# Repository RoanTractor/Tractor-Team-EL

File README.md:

# Tractor-Team-EL
Tractor team electrical , experts in killing electrical gremlins and using black powder.

To learn how to contribute
Head to Introduction and read the Introduction To Git

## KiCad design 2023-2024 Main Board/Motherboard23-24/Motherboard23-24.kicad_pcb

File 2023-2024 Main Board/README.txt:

Things Staying the same
	Safety Circuit - Not Touching That
	Safety Start - Not Touching That

Things Changing

	Minor adjustments to 
		Throttle Control
		Steering Control
	
	Layout Changes
		Bigger Board (more height, same length)

 5V Protection

	5V goes through diode to prevent the 5v and GND being swapped and messing things up
	goes through thermistor to prevent spikes of current
	Zener Diode prevents overvoltage (over 5.1V)

	Possibly Fix Fuse (i dont know if it really does anything at this moment)

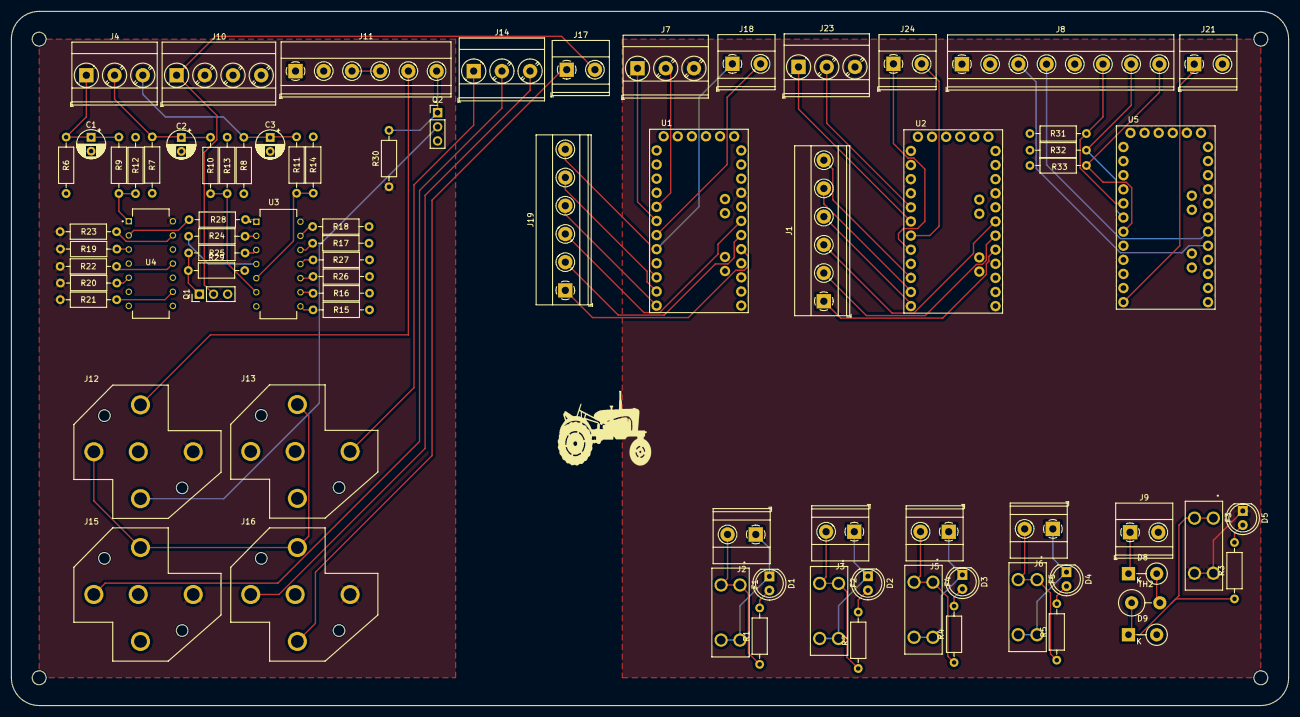
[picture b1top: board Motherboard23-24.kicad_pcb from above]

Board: 2 copper layers, 230.0 x 125.0 mm, 78 parts (0 on the bottom side), 81 nets.

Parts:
C1, C2, C3: 0.1µF; CP_Radial_D5.0mm_P2.50mm
D1, D2, D3, D4, D5: LED; LED_D5.0mm
D8: DIODE; D_DO-15_P5.08mm_Vertical_KathodeUp
D9: D_Zener; D_DO-15_P5.08mm_Vertical_KathodeUp
F1, F2, F3, F4, F5: 3568; FUSE_3568
J1, J19: Conn_01x06_Pin; TerminalBlock_Phoenix_MKDS-1,5-6-5.08_1x06_P5.08mm_Horizont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
J2, J3, J5, J6, J9, J17, J21: Conn_01x02_Male; TerminalBlock_Phoenix_MKDS-1,5-2-5.08_1x02_P5.08mm_Horizont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
J4, J14: Conn_01x03_Male; TerminalBlock_Phoenix_MKDS-3-3-5.08_1x03_P5.08mm_Horizontal
J7, J23: Conn_01x03_Pin; TerminalBlock_Phoenix_MKDS-3-3-5.08_1x03_P5.08mm_Horizontal
J8: Conn_01x08_Male; TerminalBlock_Phoenix_MKDS-1,5-8-5.08_1x08_P5.08mm_Horizont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
J10: Conn_01x04_Male; TerminalBlock_Phoenix_MKDS-3-4-5.08_1x04_P5.08mm_Horizontal
J11: Conn_01x06_Male; TerminalBlock_Phoenix_MKDS-1,5-6-5.08_1x06_P5.08mm_Horizont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
J12, J13, J15, J16: VCF4-1000; TE_VCF4-1000
J18, J24: Conn_01x02_Pin; TerminalBlock_Phoenix_MKDS-1,5-2-5.08_1x02_P5.08mm_Horizont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
Q1, Q2: Q_NMOS_GDS; PinHeader_1x03_P2.54mm_Vertical
R1, R2, R3, R4, R5, R6, R7, R8, R9, R10, R11, R19, R20, R21, R22, R23, R24, R28: 1k; R_Axial_DIN0207_L6.3mm_D2.5mm_P10.16mm_Horizontal
R12, R13, R14, R15, R16, R17, R18, R26, R27, R31, R32, R33: 10k; R_Axial_DIN0207_L6.3mm_D2.5mm_P10.16mm_Horizontal
R25: 330; R_Axial_DIN0207_L6.3mm_D2.5mm_P10.16mm_Horizontal
R29: 100k; R_Axial_DIN0207_L6.3mm_D2.5mm_P10.16mm_Horizontal
R30: 4.7k; R_Axial_DIN0207_L6.3mm_D2.5mm_P10.16mm_Horizontal
TH2: Thermistor; R_Axial_DIN0414_L11.9mm_D4.5mm_P5.08mm_Vertical
U1, U2, U5: ARDUINO_PRO_MINI; MODULE_ARDUINO_PRO_MINI
U3: CD4081BE; DIP794W45P254L1969H508Q14
U4: CD4069UBE; DIP794W45P254L1969H508Q14

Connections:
+5V: D5.1 (K), F3.2, F3.4, J7.3, J8.1, J23.3, U1.JP6_4 (VCC_1), U2.JP6_4 (VCC_1), U5.JP6_4 (VCC_1)
+12V: J10.2, J11.2, J12.30, J15.30, J16.30, R19.2, R20.1, R21.2, R22.1, R23.2, R30.1, U3.14 (VDD), U4.14 (VDD)
/Safety Circuit/Brake: C2.1, J4.2, R7.1, R10.2
/Safety Circuit/Brake_Output: R10.1, R13.1, U3.6 (D)
/Safety Circuit/Neutral: C1.1, J4.1, R6.1, R9.2
/Safety Circuit/Neutral_Inverted: R28.2, U3.1 (A)
/Safety Circuit/Neutral_Output: R9.1, R12.1, U4.1 (A)
/Safety Circuit/Seat: C3.1, J4.3, R8.1, R11.2
/Safety Circuit/Seat_Output: R11.1, R14.1, U3.5 (C)
/SafetyStart/Comp_Switch: J11.6, Q2.1 (G), R30.2
GND: C1.2, C2.2, C3.2, D9.2 (A), J8.2, J8.5, J9.2, J10.3, J10.4, J11.1, J13.85, J13.87A, J15.85, J21.2, Q1.3 (S), Q2.3 (S), R6.2, R7.2, R8.2, R12.2, R13.2, R14.2, R15.2, R16.2, R17.2, R18.2, R26.1, R27.1, R29.2, R31.2, R32.2, R33.2, U1.JP6_2 (GND_1), U1.JP7_9 (GND_2), U2.JP6_2 (GND_1), U2.JP7_9 (GND_2), U3.7 (VSS), U4.4 (~B), U4.6 (~C), U4.7 (VSS), U4.8 (~D), U4.10 (~E), U4.12 (~F), U5.JP6_2 (GND_1), U5.JP7_9 (GND_2)
unnamed: D1.2 (A), R1.2
unnamed: D1.1 (K), F1.2, F1.4, J2.1
unnamed: D2.2 (A), R2.2
unnamed: D2.1 (K), F2.2, F2.4, J3.1
unnamed: D3.2 (A), R4.2
unnamed: D3.1 (K), F4.2, F4.4, J5.1
unnamed: D4.2 (A), R5.2
unnamed: D4.1 (K), F5.2, F5.4, J6.1
unnamed: D5.2 (A), R3.2
unnamed: D8.2 (A), TH2.2
unnamed: D8.1 (K), J9.1
unnamed: D9.1 (K), F3.1, F3.3, R3.1, TH2.1
unnamed: J1.1, U2.JP6_8 (A0)
unnamed: J1.2, U2.JP6_7 (A1)
unnamed: J1.3, U2.JP6_6 (A2)
unnamed: J1.4, U2.JP7_1 (D9)
unnamed: J1.5, U2.JP7_2 (D8)
unnamed: J1.6, U2.JP7_3 (D7)
unnamed: F1.1, F1.3, J2.2, R1.1
unnamed: F2.1, F2.3, J3.2, R2.1
unnamed: F4.1, F4.3, J5.2, R4.1
unnamed: F5.1, F5.3, J6.2, R5.1
unnamed: J7.1, U1.JP7_7 (D3)
unnamed: J7.2, U1.JP7_8 (D2)
unnamed: J8.3, U5.JP6_8 (A0)
unnamed: J8.4, U5.JP6_7 (A1)
unnamed: J8.6, R31.1, U5.JP7_8 (D2)
unnamed: J8.7, R32.1, U5.JP7_7 (D3)
unnamed: J8.8, R33.1, U5.JP7_6 (D4)
unnamed: J11.3, J11.4
unnamed: J11.5, J12.86
unnamed: J12.87, J13.86, J15.86, J16.86
unnamed: J13.30, J14.1
unnamed: J14.2, J15.87
unnamed: J14.3, J16.87
unnamed: J16.85, J17.1
unnamed: J18.1, U1.JP7_5 (D5)
unnamed: J18.2, U1.JP7_6 (D4)
unnamed: J19.1, U1.JP6_8 (A0)
unnamed: J19.2, U1.JP6_7 (A1)
unnamed: J19.3, U1.JP6_6 (A2)
unnamed: J19.4, U1.JP7_1 (D9)
unnamed: J19.5, U1.JP7_2 (D8)
unnamed: J19.6, U1.JP7_3 (D7)
unnamed: J21.1, U5.JP7_1 (D9)
unnamed: J23.1, U2.JP7_7 (D3)
unnamed: J23.2, U2.JP7_8 (D2)
unnamed: J24.1, U2.JP7_5 (D5)
unnamed: J24.2, U2.JP7_6 (D4)
unnamed: Q1.1 (G), R25.2, R29.1
unnamed: J12.85, Q2.2 (D)
unnamed: U1.JP1_5 (GND), U1.JP1_6 (GND)
unnamed: U2.JP1_5 (GND), U2.JP1_6 (GND)
unnamed: R24.2, U3.2 (B)
unnamed: R15.1, U3.8 (E)
unnamed: R16.1, U3.9 (F)
unnamed: R17.1, U3.12 (G)
unnamed: R18.1, U3.13 (H)
unnamed: R25.1, U3.3 (J=A.B)
unnamed: R24.1, U3.4 (K=C.D)
unnamed: R26.2, U3.10 (L=E.F)
unnamed: R27.2, U3.11 (M=G.M)
unnamed: R19.1, U4.3 (B)
unnamed: R20.2, U4.5 (C)
unnamed: R21.1, U4.9 (D)
unnamed: R22.2, U4.11 (E)
unnamed: R23.1, U4.13 (F)
unnamed: R28.1, U4.2 (~A)
unnamed: U5.JP1_5 (GND), U5.JP1_6 (GND)
Safety_Signal: J10.1, J17.2, Q1.2 (D)

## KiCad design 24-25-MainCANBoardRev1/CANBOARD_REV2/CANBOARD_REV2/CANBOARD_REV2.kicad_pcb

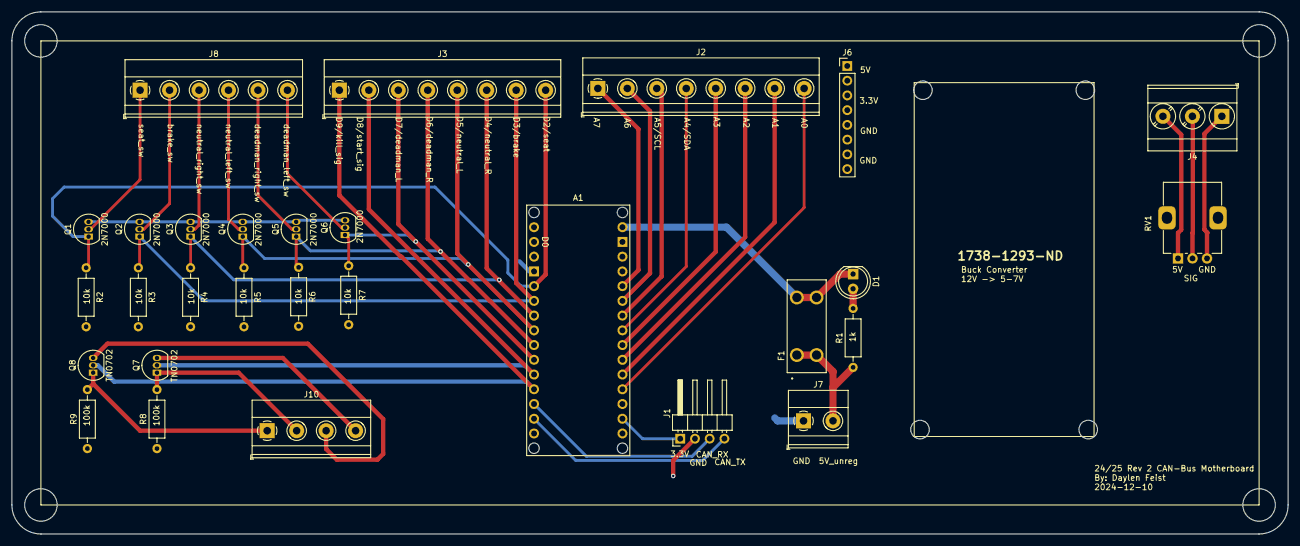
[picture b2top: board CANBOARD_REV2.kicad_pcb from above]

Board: 2 copper layers, 220.0 x 90.0 mm, 29 parts (0 on the bottom side), 37 nets.

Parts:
A1: Arduino_Nano_ESP32_Socket
D1: LED; LED_D5.0mm
F1: 3568; FUSE_3568
J1: Conn_01x04_Pin; PinHeader_1x04_P2.54mm_Horizontal
J2, J3: Conn_01x08_Male; TerminalBlock_Phoenix_MKDS-1,5-8-5.08_1x08_P5.08mm_Horizont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
J4: Conn_01x03_Male; TerminalBlock_Phoenix_MKDS-3-3-5.08_1x03_P5.08mm_Horizontal
J6: Conn_01x08_Pin; PinHeader_1x08_P2.54mm_Vertical
J7: Conn_01x02_Pin; TerminalBlock_Phoenix_MKDS-1,5-2-5.08_1x02_P5.08mm_Horizont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
J8: Conn_01x06_Male; TerminalBlock_Phoenix_MKDS-1,5-6-5.08_1x06_P5.08mm_Horizont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
J10: Conn_01x04_Pin; TerminalBlock_Phoenix_MKDS-1,5-4-5.08_1x04_P5.08mm_Horizont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
Q1, Q2, Q3, Q4, Q5, Q6: 2N7000; TO-92_Inline
Q7, Q8: TN0702; TO-92_Inline
R1: 1k; R_Axial_DIN0207_L6.3mm_D2.5mm_P10.16mm_Horizontal
R2, R3, R4, R5, R6, R7: 10k; R_Axial_DIN0207_L6.3mm_D2.5mm_P10.16mm_Horizontal
R8, R9: 100k; R_Axial_DIN0207_L6.3mm_D2.5mm_P10.16mm_Horizontal
RV1: R_Potentiometer; Potentiometer_Alps_RK09K_Single_Vertical

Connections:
+3V3: A1.3V3 (3.3V), J1.1, J6.3, J6.4, Q1.3 (D), Q2.3 (D), Q3.3 (D), Q4.3 (D), Q5.3 (D), Q6.3 (D)
+5V: A1.5V, J6.1, J6.2
/Arduino/A0: A1.A0, J2.8
/Arduino/A1: A1.A1, J2.7
/Arduino/A2: A1.A2, J2.6
/Arduino/A3: A1.A3, J2.5
/Arduino/A4/SDA: A1.A4 (A4/SDA), J2.4
/Arduino/A5/SCL: A1.A5 (A5/SCL), J2.3
/Arduino/A6: A1.A6, J2.2
/Arduino/A7: A1.A7, J2.1
/Arduino/CAN_RX: A1.D10, J1.3
/Arduino/CAN_TX: A1.D11 (D11_MOSI), J1.4
/Arduino/kill_vin: J10.3, Q8.3 (D)
/Arduino/kill_vout: J10.1, Q8.1 (S), R9.2
/Arduino/starter_vin: J10.4, Q7.3 (D)
/Arduino/starter_vout: J10.2, Q7.1 (S), R8.2
/Input_Power/V_in_unreg: F1.1, F1.3, J7.2, R1.1
/Safety Circuitry/brake_switch: J8.2, Q2.2 (G)
/Safety Circuitry/deadman_left_switch: J8.6, Q6.2 (G)
/Safety Circuitry/deadman_right_switch: J8.5, Q5.2 (G)
/Safety Circuitry/neutral_left_switch: J8.4, Q4.2 (G)
/Safety Circuitry/neutral_right_switch: J8.3, Q3.2 (G)
/Safety Circuitry/seat_switch: J8.1, Q1.2 (G)
/Throttle/Accel_GND: J4.1, RV1.3
/Throttle/Accel_power: J4.3, RV1.1
/Throttle/Accel_sig: J4.2, RV1.2
GND: A1.GND1 (GND), A1.GND2 (GND), J1.2, J6.5, J6.6, J6.7, J6.8, J7.1, R2.2, R3.2, R4.2, R5.2, R6.2, R7.2, R8.1, R9.1
unnamed: D1.2 (A), R1.2
V_in: A1.VIN, D1.1 (K), F1.2, F1.4
brake_signal: A1.D3, J3.7, Q2.1 (S), R3.1
deadman_left: A1.D7, J3.3, Q6.1 (S), R7.1
deadman_right: A1.D6, J3.4, Q5.1 (S), R6.1
kill_sig: A1.D9, J3.1, Q8.2 (G)
neutral_left: A1.D5, J3.5, Q4.1 (S), R5.1
neutral_right: A1.D4, J3.6, Q3.1 (S), R4.1
seat_signal: A1.D2, J3.8, Q1.1 (S), R2.1
start_sig: A1.D8, J3.2, Q7.2 (G)

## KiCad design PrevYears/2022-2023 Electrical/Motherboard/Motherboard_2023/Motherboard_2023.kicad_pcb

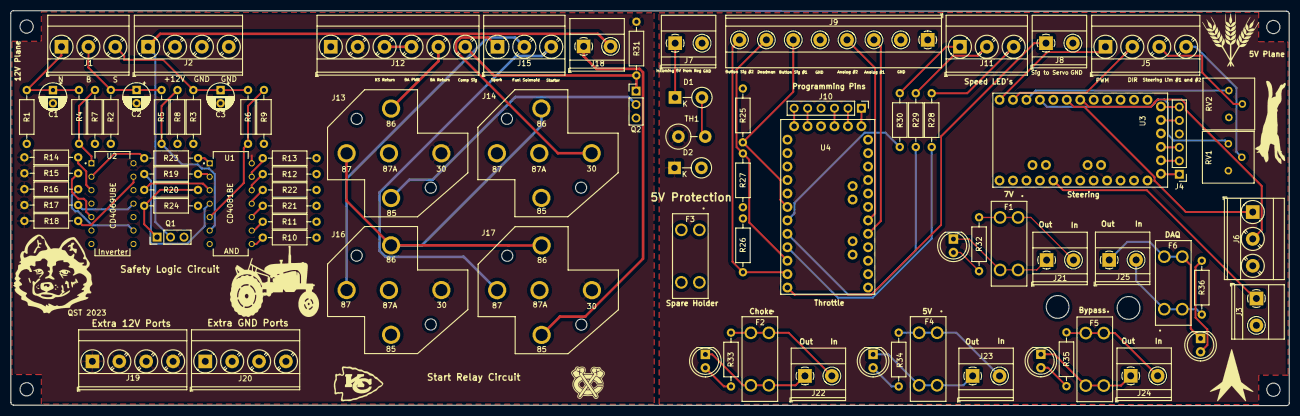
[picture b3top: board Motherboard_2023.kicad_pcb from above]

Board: 2 copper layers, 241.5 x 74.6 mm, 86 parts (0 on the bottom side), 82 nets.

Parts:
C1, C2, C3: 0.1µF; CP_Radial_D5.0mm_P2.50mm
D1: DIODE; D_DO-15_P5.08mm_Vertical_KathodeUp
D2: D_Zener; D_DO-15_P5.08mm_Vertical_KathodeUp
D3, D4, D5, D6, D7: LED; LED_D5.0mm
F1, F2, F4, F5, F6: 3568; FUSE_3568
F3: Fuse; FUSE_3568
J1, J6, J11, J15: Conn_01x03_Male; TerminalBlock_Phoenix_MKDS-3-3-5.08_1x03_P5.08mm_Horizontal
J2, J5, J19, J20: Conn_01x04_Male; TerminalBlock_Phoenix_MKDS-3-4-5.08_1x04_P5.08mm_Horizontal
J3, J7, J8, J18, J21, J22, J23, J24, J25: Conn_01x02_Male; TerminalBlock_Phoenix_MKDS-1,5-2-5.08_1x02_P5.08mm_Horizont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
J4, J10: Conn_01x06_Male; PinHeader_1x06_P2.54mm_Vertical
J9: Conn_01x08_Male; TerminalBlock_Phoenix_MKDS-1,5-8-5.08_1x08_P5.08mm_Horizont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
J12: Conn_01x06_Male; TerminalBlock_Phoenix_MKDS-3-6-5.08_1x06_P5.08mm_Horizontal
J13, J14, J16, J17: VCF4-1000; TE_VCF4-1000
Q1, Q2: Q_NMOS_GDS; PinHeader_1x03_P2.54mm_Vertical
R1, R2, R3, R4, R5, R6, R14, R15, R16, R17, R18, R19, R23, R32, R33, R34, R35, R36: 1k; R_Axial_DIN0207_L6.3mm_D2.5mm_P10.16mm_Horizontal
R7, R8, R9, R10, R11, R12, R13, R21, R22: 10k; R_Axial_DIN0207_L6.3mm_D2.5mm_P10.16mm_Horizontal
R20: 330; R_Axial_DIN0207_L6.3mm_D2.5mm_P10.16mm_Horizontal
R24: 100k; R_Axial_DIN0207_L6.3mm_D2.5mm_P10.16mm_Horizontal
R25, R26, R27, R28, R29, R30: R; R_Axial_DIN0207_L6.3mm_D2.5mm_P10.16mm_Horizontal
R31: 4.7k; R_Axial_DIN0207_L6.3mm_D2.5mm_P10.16mm_Horizontal
RV1, RV2: R_POT_TRIM; Potentiometer_Bourns_3386P_Vertical
TH1: Thermistor; R_Axial_DIN0414_L11.9mm_D4.5mm_P5.08mm_Vertical
U1: CD4081BE; DIP794W45P254L1969H508Q14
U2: CD4069UBE; DIP794W45P254L1969H508Q14
U3, U4: ARDUINO_PRO_MINI; MODULE_ARDUINO_PRO_MINI

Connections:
+5V: D2.1, J6.3, J9.1, TH1.1, U3.JP6_4, U4.JP6_4
+12V: J2.2, J12.2, J13.30, J16.30, J17.30, J19.1, J19.2, J19.3, J19.4, R14.2, R15.1, R16.2, R17.1, R18.2, R31.1, U1.14, U2.14
/Safety Circuit /Brake: C2.1, J1.2, R2.1, R5.2
/Safety Circuit /Brake_Output: R5.1, R8.1, U1.6
/Safety Circuit /Neutral: C1.1, J1.1, R1.1, R4.2
/Safety Circuit /Neutral_Inverted: R23.2, U1.1
/Safety Circuit /Neutral_Output: R4.1, R7.1, U2.1
/Safety Circuit /Seat: C3.1, J1.3, R3.1, R6.2
/Safety Circuit /Seat_Output: R6.1, R9.1, U1.5
/Safety Start /Comp_Switch: J12.6, Q2.1, R31.2
GND: C1.2, C2.2, C3.2, D2.2, J2.3, J2.4, J3.2, J7.2, J8.2, J9.2, J9.5, J12.1, J14.85, J14.87A, J16.85, J20.1, J20.2, J20.3, J20.4, Q1.3, Q2.3, R1.2, R2.2, R3.2, R7.2, R8.2, R9.2, R10.2, R11.2, R12.2, R13.2, R21.1, R22.1, R24.2, R25.2, R26.1, R27.1, RV1.1, RV2.1, U1.7, U2.4, U2.6, U2.7, U2.8, U2.10, U2.12, U3.JP6_2, U3.JP7_9, U4.JP6_2, U4.JP7_9
unnamed: D1.1, J7.1
unnamed: D1.2, TH1.2
unnamed: D3.1, F1.2, F1.4, J21.1
unnamed: D3.2, R32.1
unnamed: D4.1, F2.2, F2.4, J22.1
unnamed: D4.2, R33.1
unnamed: D5.1, F4.2, F4.4, J23.1
unnamed: D5.2, R34.1
unnamed: D6.1, F5.2, F5.4, J24.1
unnamed: D6.2, R35.1
unnamed: D7.1, F6.2, F6.4, J25.1
unnamed: D7.2, R36.1
unnamed: F1.1, F1.3, J21.2, R32.2
unnamed: F2.1, F2.3, J22.2, R33.2
unnamed: F4.1, F4.3, J23.2, R34.2
unnamed: F5.1, F5.3, J24.2, R35.2
unnamed: F6.1, F6.3, J25.2, R36.2
unnamed: J3.1, U3.JP6_8
unnamed: J4.1, U3.JP1_1
unnamed: J4.2, U3.JP1_2
unnamed: J4.3, U3.JP1_3
unnamed: J4.5, J4.6, U3.JP1_5, U3.JP1_6
unnamed: J5.1, U3.JP7_1
unnamed: J5.2, U3.JP7_2
unnamed: J5.3, RV2.2
unnamed: J5.4, RV1.2
unnamed: J6.1, U3.JP7_6
unnamed: J6.2, U3.JP7_7
unnamed: J8.1, U4.JP7_1
unnamed: J9.3, U4.JP6_8
unnamed: J9.4, U4.JP6_7
unnamed: J9.6, R25.1, U4.JP7_7
unnamed: J9.7, R27.2, U4.JP7_3
unnamed: J9.8, R26.2, U4.JP7_2
unnamed: J10.1, U4.JP1_1
unnamed: J10.2, U4.JP1_2
unnamed: J10.3, U4.JP1_3
unnamed: J10.5, J10.6, U4.JP1_5, U4.JP1_6
unnamed: J11.1, R30.2
unnamed: J11.2, R29.2
unnamed: J11.3, R28.2
unnamed: J12.3, J12.4
unnamed: J12.5, J13.86
unnamed: J13.85, Q2.2
unnamed: J13.87, J14.86, J16.86, J17.86
unnamed: J14.30, J15.1
unnamed: J15.2, J16.87
unnamed: J15.3, J17.87
unnamed: J17.85, J18.1
unnamed: Q1.1, R20.2, R24.1
unnamed: R10.1, U1.8
unnamed: R11.1, U1.9
unnamed: R12.1, U1.12
unnamed: R13.1, U1.13
unnamed: R14.1, U2.3
unnamed: R15.2, U2.5
unnamed: R16.1, U2.9
unnamed: R17.2, U2.11
unnamed: R18.1, U2.13
unnamed: R19.1, U1.4
unnamed: R19.2, U1.2
unnamed: R20.1, U1.3
unnamed: R21.2, U1.10
unnamed: R22.2, U1.11
unnamed: R23.1, U2.2
unnamed: R28.1, U4.JP7_4
unnamed: R29.1, U4.JP7_5
unnamed: R30.1, U4.JP7_6
unnamed: RV1.3, U3.JP7_4
unnamed: RV2.3, U3.JP7_3
Safety_Signal: J2.1, J18.2, Q1.2

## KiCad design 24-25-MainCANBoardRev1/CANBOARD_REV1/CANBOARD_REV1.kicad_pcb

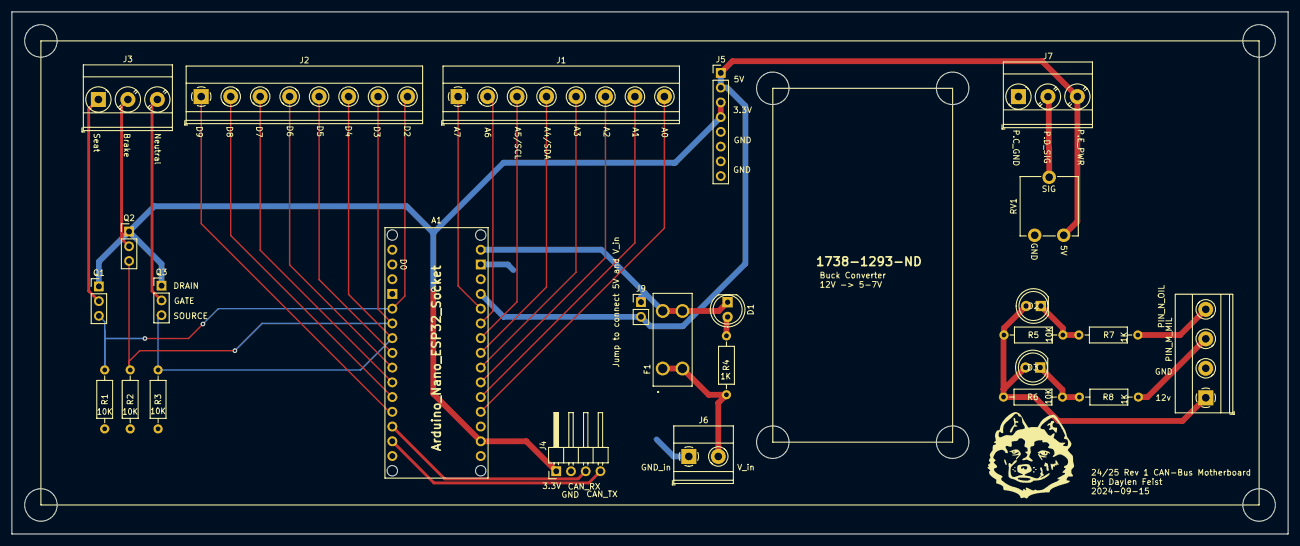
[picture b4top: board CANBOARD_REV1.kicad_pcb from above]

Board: 2 copper layers, 220.0 x 90.0 mm, 26 parts (0 on the bottom side), 33 nets.

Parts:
A1: Arduino_Nano_ESP32_Socket
D1, D2, D3: LED; LED_D5.0mm
F1: 3568; FUSE_3568
J1, J2: Conn_01x08_Male; TerminalBlock_Phoenix_MKDS-1,5-8-5.08_1x08_P5.08mm_Horizont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
J3, J7: Conn_01x03_Male; TerminalBlock_Phoenix_MKDS-3-3-5.08_1x03_P5.08mm_Horizontal
J4: Conn_01x04_Pin; PinHeader_1x04_P2.54mm_Horizontal
J5: Conn_01x08_Pin; PinHeader_1x08_P2.54mm_Vertical
J6: Conn_01x02_Pin; TerminalBlock_Phoenix_MKDS-1,5-2-5.08_1x02_P5.08mm_Horizont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
J8: Conn_01x04_Pin; TerminalBlock_Phoenix_MKDS-1,5-4-5.08_1x04_P5.08mm_Horizont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
J9: Conn_01x02_Pin; PinHeader_1x02_P2.54mm_Vertical
Q1, Q2, Q3: NMOS; PinHeader_1x03_P2.54mm_Vertical
R1, R2, R3, R5, R6: 10k; R_Axial_DIN0207_L6.3mm_D2.5mm_P10.16mm_Horizontal
R4: 1k; R_Axial_DIN0207_L6.3mm_D2.5mm_P10.16mm_Horizontal
R7, R8: 1K; R_Axial_DIN0207_L6.3mm_D2.5mm_P10.16mm_Horizontal
RV1: R_Potentiometer; Potentiometer_ACP_CA9-V10_Vertical

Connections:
+3V3: A1.3V3 (3.3V), J4.1, J5.3, J5.4, Q1.1 (D), Q2.1 (D), Q3.1 (D)
+5V: A1.5V, J5.1, J5.2, J7.3, J9.2, RV1.1
+12V: D2.2 (A), D3.2 (A), J8.1, R5.2, R6.2
/A0: A1.A0, J1.8
/A1: A1.A1, J1.7
/A2: A1.A2, J1.6
/A3: A1.A3, J1.5
/A4/SDA: A1.A4 (A4/SDA), J1.4
/A5/SCL: A1.A5 (A5/SCL), J1.3
/A6: A1.A6, J1.2
/A7: A1.A7, J1.1
/Accel_sig: J7.2, RV1.2
/Brake: J3.2, Q2.2 (G)
/CAN_RX: A1.D10, J4.3
/CAN_TX: A1.D11 (D11_MOSI), J4.4
/D2: A1.D2, J2.8, Q1.3 (S), R1.1
/D3: A1.D3, J2.7, Q2.3 (S), R2.1
/D4: A1.D4, J2.6, Q3.3 (S), R3.1
/D5: A1.D5, J2.5
/D6: A1.D6, J2.4
/D7: A1.D7, J2.3
/D8: A1.D8, J2.2
/D9: A1.D9, J2.1
/Neutral: J3.3, Q3.2 (G)
/PIN_M_MIL: J8.3, R8.1
/PIN_N_Oil: J8.4, R7.1
/Seat: J3.1, Q1.2 (G)
/V_in: A1.VIN, D1.1 (K), F1.2, F1.4, J9.1
/V_in_unreg: F1.1, F1.3, J6.2, R4.1
GND: A1.GND1 (GND), A1.GND2 (GND), J4.2, J5.5, J5.6, J5.7, J5.8, J6.1, J7.1, J8.2, R1.2, R2.2, R3.2, RV1.3
unnamed: D1.2 (A), R4.2
unnamed: D2.1 (K), R5.1, R7.2
unnamed: D3.1 (K), R6.1, R8.2

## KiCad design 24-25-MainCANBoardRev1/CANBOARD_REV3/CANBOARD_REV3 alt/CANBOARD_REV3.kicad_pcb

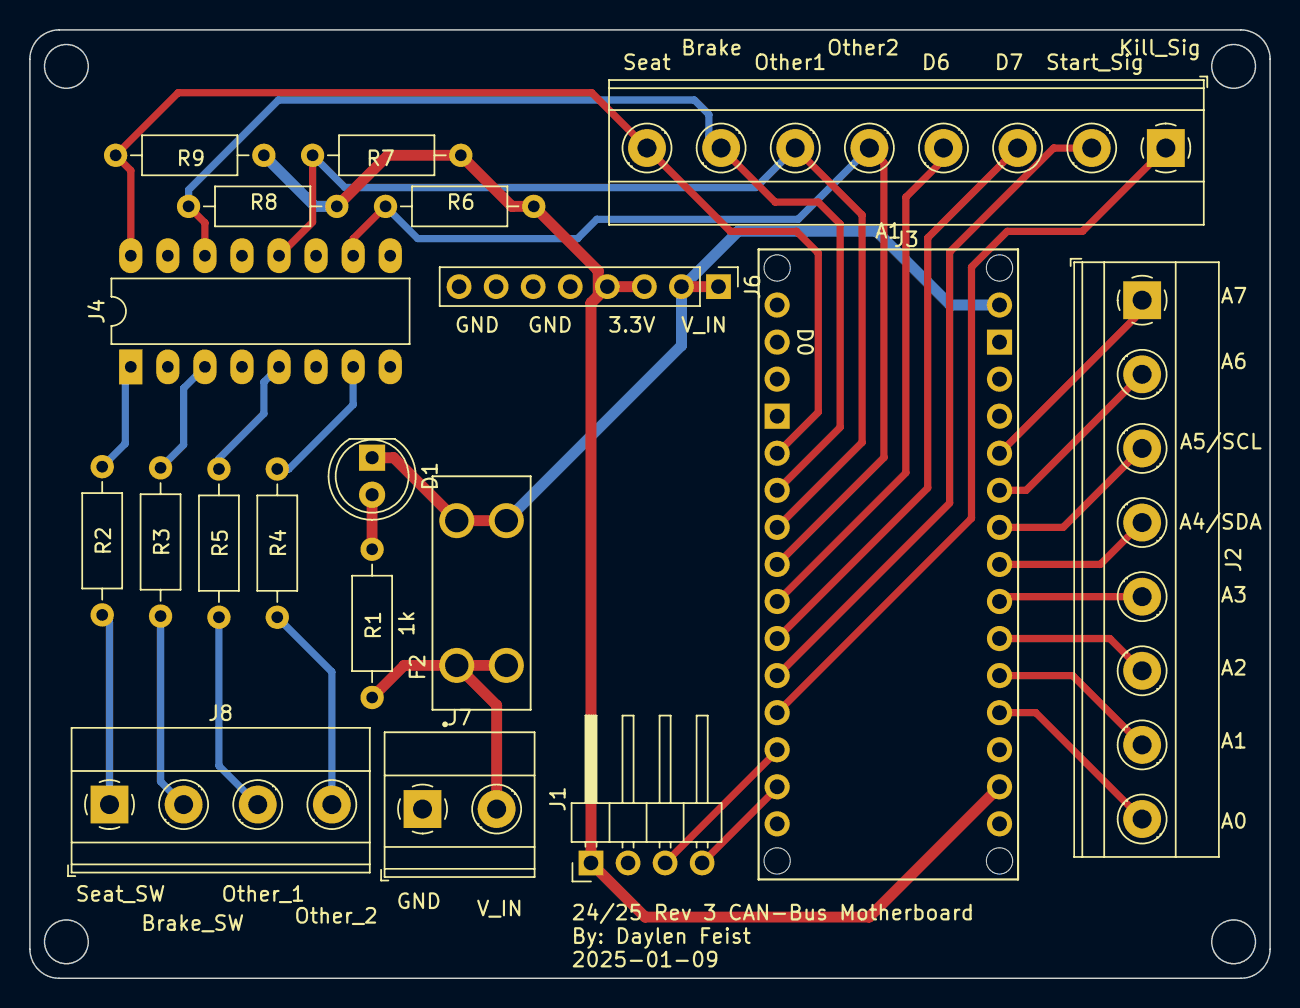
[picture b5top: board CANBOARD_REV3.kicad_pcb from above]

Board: 2 copper layers, 85.0 x 65.0 mm, 19 parts (0 on the bottom side), 31 nets.

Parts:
A1: Arduino_Nano_ESP32_Socket
D1: LED; LED_D5.0mm
F2: 3568; FUSE_3568
J1: Conn_01x04_Pin; PinHeader_1x04_P2.54mm_Horizontal
J2, J3: Conn_01x08_Male; TerminalBlock_Phoenix_MKDS-1,5-8-5.08_1x08_P5.08mm_Horizont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
J4: PC847X5J000F; DIP-16_W7.62mm_LongPads
J6: Conn_01x08_Pin; PinHeader_1x08_P2.54mm_Vertical
J7: Conn_01x02_Pin; TerminalBlock_Phoenix_MKDS-1,5-2-5.08_1x02_P5.08mm_Horizont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
J8: Conn_01x04_Male; TerminalBlock_Phoenix_MKDS-1,5-4-5.08_1x04_P5.08mm_Horizont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
R1: 1k; R_Axial_DIN0207_L6.3mm_D2.5mm_P10.16mm_Horizontal
R2, R3, R4, R5, R6, R7, R8, R9: 10k; R_Axial_DIN0207_L6.3mm_D2.5mm_P10.16mm_Horizontal

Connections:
+3V3: A1.3V3 (3.3V), J1.1, J6.3, J6.4, R6.2, R7.2, R8.2, R9.2
/Arduino/A0: A1.A0, J2.8
/Arduino/A1: A1.A1, J2.7
/Arduino/A2: A1.A2, J2.6
/Arduino/A3: A1.A3, J2.5
/Arduino/A4/SDA: A1.A4 (A4/SDA), J2.4
/Arduino/A5/SCL: A1.A5 (A5/SCL), J2.3
/Arduino/A6: A1.A6, J2.2
/Arduino/A7: A1.A7, J2.1
/Arduino/CAN_RX: A1.D10, J1.3
/Arduino/CAN_TX: A1.D11 (D11_MOSI), J1.4
/Arduino/D6: A1.D6, J3.4
/Arduino/D7: A1.D7, J3.3
/Input_Power/V_in_unreg: F2.1, F2.3, J7.2, R1.1
/Safety Circuitry/brake_switch: J8.2, R3.2
/Safety Circuitry/other_sw1: J8.3, R5.2
/Safety Circuitry/other_sw2: J8.4, R4.2
/Safety Circuitry/seat_switch: J8.1, R2.2
GND: A1.GND1 (GND), A1.GND2 (GND), J1.2, J4.2, J4.4, J4.6, J4.8, J4.9, J4.11, J4.13, J4.15, J6.5, J6.6, J6.7, J6.8, J7.1
unnamed: D1.2 (A), R1.2
unnamed: J4.1, R2.1
unnamed: J4.3, R3.1
unnamed: J4.5, R5.1
unnamed: J4.7, R4.1
VCC: A1.VIN, D1.1 (K), F2.2, F2.4, J6.1, J6.2
brake_signal: A1.D3, J3.7, J4.14, R8.1
kill_sig: A1.D9, J3.1
other_sw1_sig: A1.D4, J3.6, J4.12, R7.1
other_sw2_sig: A1.D5, J3.5, J4.10, R6.1
seat_signal: A1.D2, J3.8, J4.16, R9.1
start_sig: A1.D8, J3.2

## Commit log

2023-11-18 First Commit!
2023-11-18 Added my name
2023-11-18 created introductions folder
2023-11-18 alex_file added
2023-11-18 cain_file added
2023-11-18 roan_file
2023-11-18 created folder for 2022-2023
2023-11-18 added some text to Alex file
2023-11-18 Created SubProjects
2023-11-18 Updated Introduction File To Add Instructions
2023-11-18 text blurb
2023-11-25 Create 2022-2023 Steering Folder
2023-11-25 Added Steering Files
2023-11-25 Create Motherboard folder
2023-11-25 The Ki-CAD files for the Motherboard
2023-11-26 Created Motherboard skeleton and libraries
2023-11-27 Added Sheets and Fuses
2023-12-02 Added Schematic for Steering and Throttle
2023-12-09 Close to finishing up 2023-2024 Main Board Schematic
2023-12-14 Added BOM
2023-12-17 first draft of 23-24 Main Board
2023-12-17 Added Pictures
2023-12-17 added Bill of materials
2025-01-17 Added pcb files
